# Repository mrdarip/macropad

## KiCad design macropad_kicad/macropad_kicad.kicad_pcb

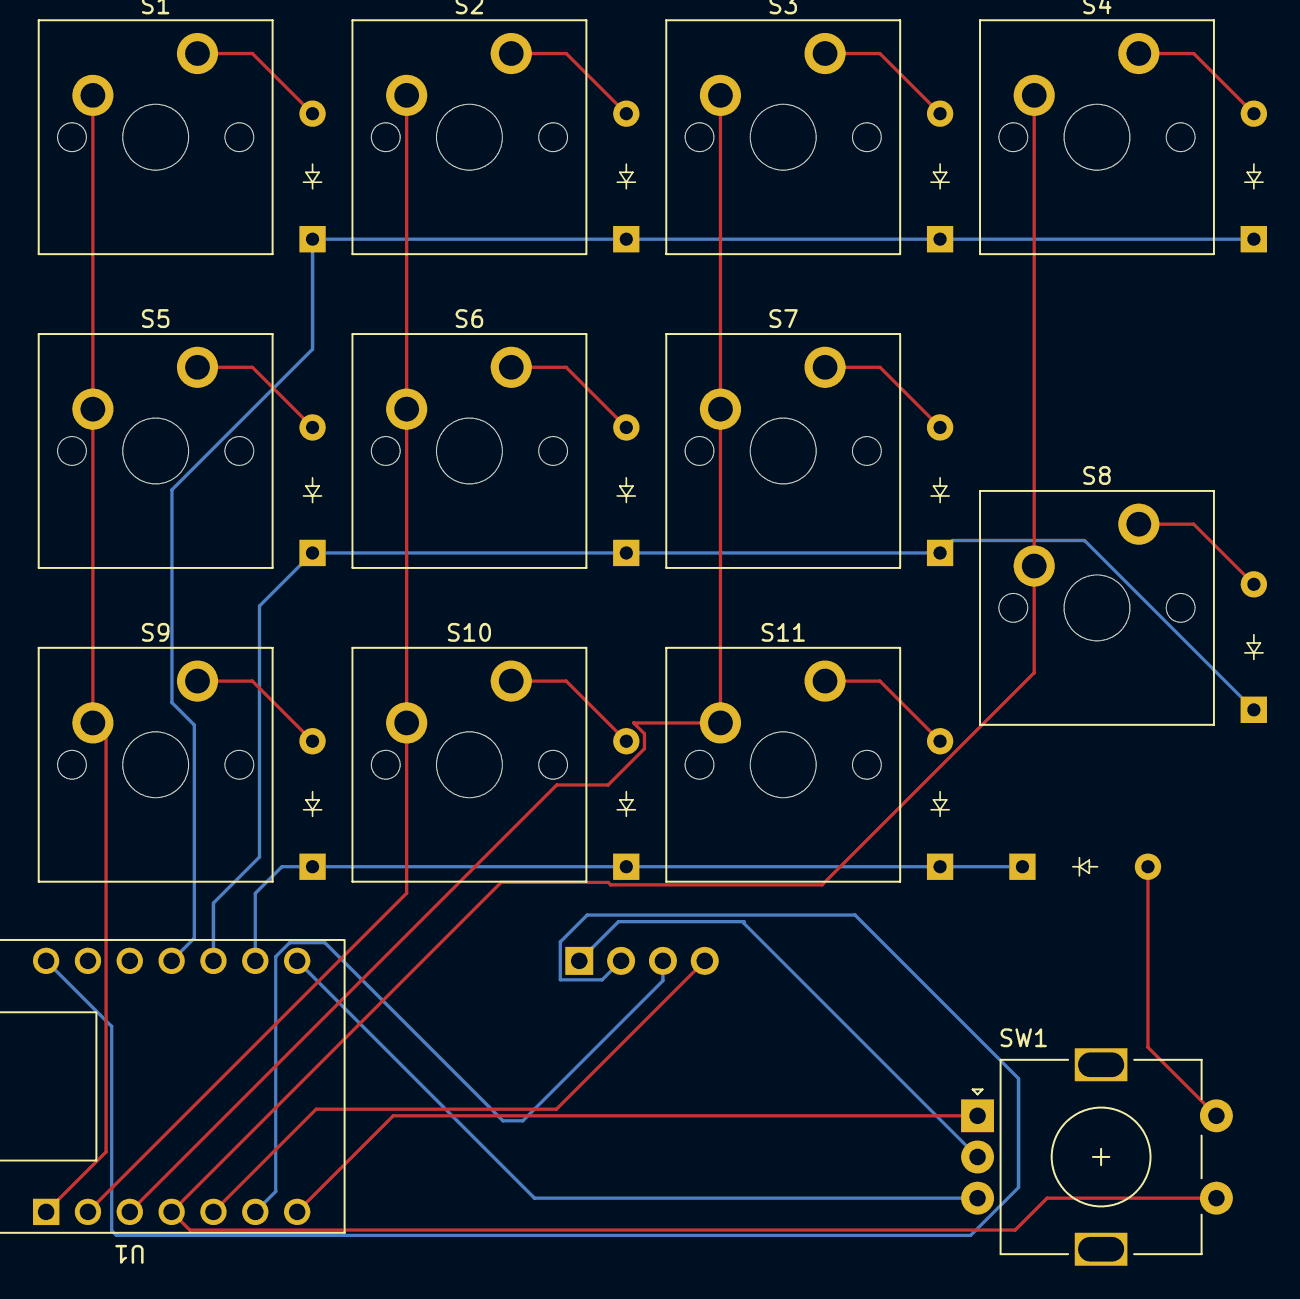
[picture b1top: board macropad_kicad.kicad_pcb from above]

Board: 2 copper layers, 26 parts (0 on the bottom side), 25 nets.

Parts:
D1, D2, D3, D4, D5, D6, D7, D8, D9, D10, D11, D12: Diode; Diode_DO-35
J1: OLED_128x64
S1, S2, S3, S4, S5, S6, S7, S8, S9, S10, S11: Keyswitch; MX_PCB_1.00u
SW1: RotaryEncoder_Switch; RotaryEncoder_Alps_EC11E-Switch_Vertical_H20mm
U1: MOUDLE-SEEEDUINO-XIAO; MOUDLE14P-2.54-21X17.8MM

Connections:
+5V: J1.2 (VCC), U1.14 (5V)
Col 0: S1.1, S5.1, S9.1, U1.1 (PA02_A0_D0)
Col 1: S2.1, S6.1, S10.1, U1.2 (PA4_A1_D1)
Col 2: S3.1, S7.1, S11.1, U1.3 (PA10_A2_D2)
Col 3: S4.1, S8.1, SW1.S1, U1.4 (PA11_A3_D3)
GND: J1.1 (GND), SW1.C, U1.13 (GND)
unnamed: D1.2 (A), S1.2
unnamed: D2.2 (A), S2.2
unnamed: D3.2 (A), S3.2
unnamed: D4.2 (A), S4.2
unnamed: D5.2 (A), S5.2
unnamed: D6.2 (A), S6.2
unnamed: D7.2 (A), S7.2
unnamed: D8.2 (A), S8.2
unnamed: D9.2 (A), S9.2
unnamed: D10.2 (A), S10.2
unnamed: D11.2 (A), S11.2
unnamed: D12.2 (A), SW1.S2
Rot A: SW1.A, U1.7 (PB08_A6_D6_TX)
Rot B: SW1.B, U1.8 (PB09_A7_D7_RX)
Row 0: D1.1 (K), D2.1 (K), D3.1 (K), D4.1 (K), U1.11 (PA6_A10_D10_MOSI)
Row 1: D5.1 (K), D6.1 (K), D7.1 (K), D8.1 (K), U1.10 (PA5_A9_D9_MISO)
Row 2: D9.1 (K), D10.1 (K), D11.1 (K), D12.1 (K), U1.9 (PA7_A8_D8_SCK)
SCL: J1.3 (SCL), U1.6 (PA9_A5_D5_SCL)
SDA: J1.4 (SDA), U1.5 (PA8_A4_D4_SDA)

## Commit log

2025-02-05 Created schematic with matrix and OLED display The rotary encoders are not connected yet
2025-02-08 Add schematic for matrix and OLED display integration Re-Implemented schematic as there in not enough pins
2025-02-08 Update footprint properties and library URI in schematic files created pcb with footprints
2025-02-08 fixed scheme
2025-02-08 routed all wires manually
2025-02-09 added silkscreen images
2025-02-10 fixed silkscreen
2025-02-10 added that copper cool effect thing
2025-02-10 exported for production
2025-02-10 recreated file structure for later shipment
2025-02-15 completed case scad
2025-02-15 corrected case rotation for later 3d printing
2025-02-15 prepared file structure for production and exported 3d files
2025-02-15 created firmware
2025-02-15 created readme.md
2025-02-15 fixed naming for launch
2025-02-15 fixed pcb
2025-04-13 added new silkscreen text and adjusted position of existing text on PCB layout
